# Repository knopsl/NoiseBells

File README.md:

# Noise Bells synthesizer module

This is a percussion and drone synth module based on ideas presented in the 2015 Hackaday article "[Logic noise: More CMOS cowbell!](https://hackaday.com/2015/04/10/logic-noise-more-cmos-cowbell/)" by Elliot Williams. The PCB and front panel are Kosmo format but the same circuit could be implemented in Eurorack format, or other ±12V formats, with no changes other than PCB, panel, and jack dimensions.

The module consists of two separate sections. One is a 2-oscillator circuit based on the "cowbell" section of the Hackaday article. The other is a 4-oscillator circuit, lying sort of halfway between the "cowbell" and "hi hat" designs and designed to use most of the IC functionality left over from the "cowbell" side. Whether it leans more toward bell or cymbal sounds I leave for you to decide. The two sections differ only in the number of oscillators and XORs used.

Aside from a few component value changes, notably a larger capacitor allowing longer decay times, there are a couple of significant modifications to Williams's design:

* The 2-diode "VCA" has been replaced by a 4066 analog switch "VCA" as discussed in the article's comments and at [http://files.electro-music.com/forum/viewtopic.php?highlight=diode+vca&t=23960](http://files.electro-music.com/forum/viewtopic.php?highlight=diode+vca&t=23960). 
* A switch has been added to bypass the EG/VCA section, sending the output of the final XOR straight to the output buffer. This allows using the module for noisy drones.

Pots are used for variable oscillator frequencies and amplitude envelope decay rates. Trigger B input is normalled to Trigger A.

For BOM, schematics, and PCB layout see the [Docs](Docs) folder. The build should be entirely straightforward except, on the first run boards, for the issues mentioned below. Presumably any small signal NPN transistor can be substituted for the 2N3904, though I have not tested any others. 

**Note:** On the first run PCBs the delay pots are connected incorrectly. To fix this, bend the middle leg up and solder it to the leg on its right (pin 2 to pin 3):

This is only for the two delay pots. The six oscillator frequency pots are okay.

Also two capacitors are marked '10uF (47uF?)'. These are 10µF. Unless you like 47µF better of course.

These problems are corrected in the current version.

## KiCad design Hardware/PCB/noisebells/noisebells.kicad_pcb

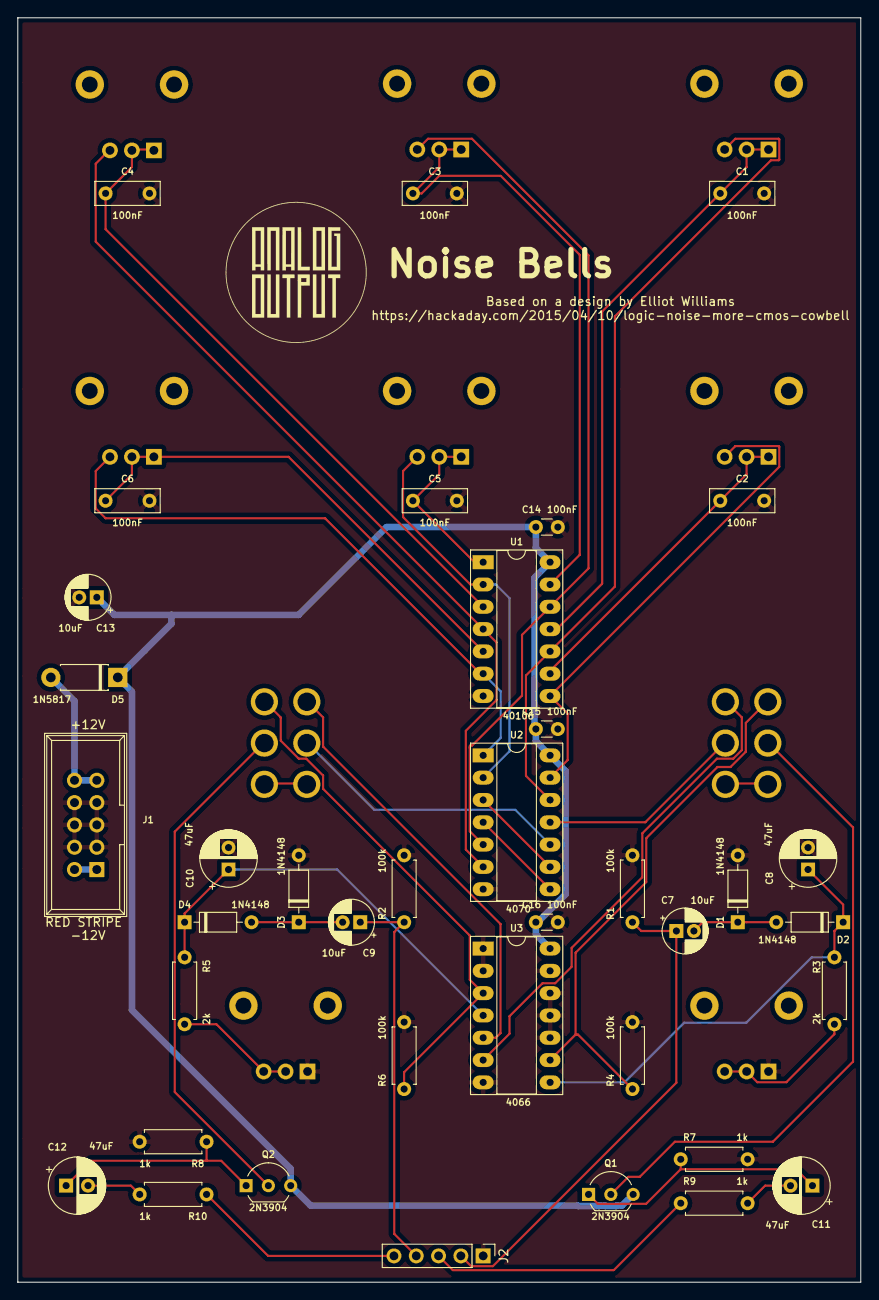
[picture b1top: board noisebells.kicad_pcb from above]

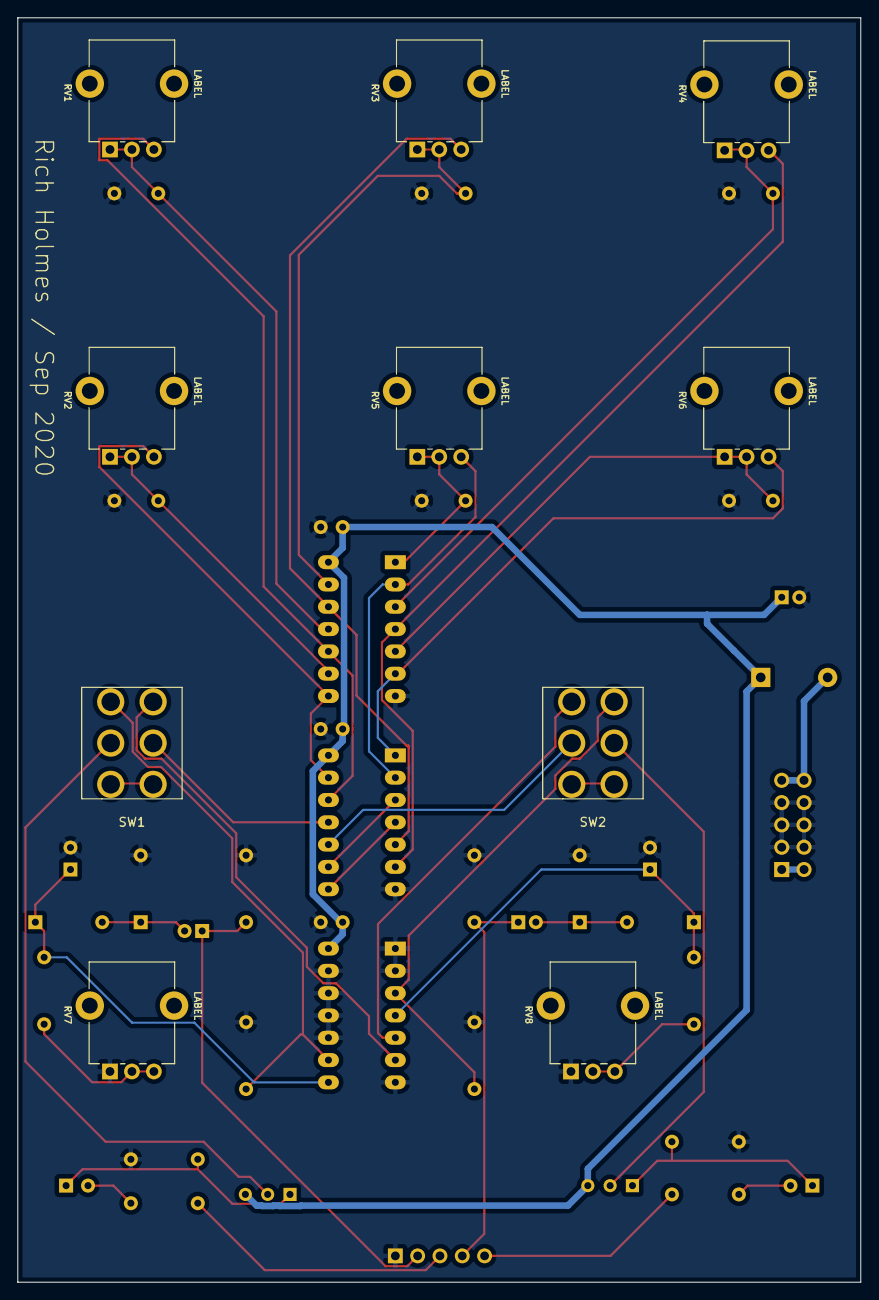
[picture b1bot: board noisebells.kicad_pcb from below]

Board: 2 copper layers, 96.0 x 144.0 mm, 48 parts (10 on the bottom side), 42 nets.

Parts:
C1, C2, C3, C4, C5, C6: 100nF; C_Rect_L7.2mm_W2.5mm_P5.00mm_FKS2_FKP2_MKS2_MKP2
C7, C9, C13: 10uF; CP_Radial_D5.0mm_P2.00mm
C8, C10, C11, C12: 47uF; CP_Radial_D6.3mm_P2.50mm
C14, C15, C16: 100nF; C_Disc_D3.0mm_W1.6mm_P2.50mm
D1, D2, D3, D4: 1N4148; D_DO-35_SOD27_P7.62mm_Horizontal
D5: 1N5817; D_DO-41_SOD81_P7.62mm_Horizontal
J1: Synth_power_2x5; Power_Header
J2: Conn_01x05; PinHeader_1x05_P2.54mm_Vertical
Q1, Q2: 2N3904; TO-92_Inline_Wide
R1, R2, R4, R6: 100k; R_Axial_DIN0207_L6.3mm_D2.5mm_P7.62mm_Horizontal
R3, R5: 2k; R_Axial_DIN0207_L6.3mm_D2.5mm_P7.62mm_Horizontal
R7, R8, R9, R10: 1k; R_Axial_DIN0207_L6.3mm_D2.5mm_P7.62mm_Horizontal
RV1, RV2, RV3, RV4, RV5, RV6, RV7, RV8: 100k; Potentiometer_Alpha_RD901F-40-00D_Single_Vertical_CircularH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
SW1, SW2: SW_DPDT_x2; DPDT-toggle-switch-1M-seriesx
U1: 40106; DIP-14_W7.62mm_Socket_LongPads
U2: 4070; DIP-14_W7.62mm_Socket_LongPads
U3: 4066; DIP-14_W7.62mm_Socket_LongPads

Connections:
+12V: C13.1, C14.1, C15.1, C16.1, D5.1, Q1.3, Q2.3, U1.14, U2.14, U3.14
GND: C1.2, C2.2, C3.2, C4.2, C5.2, C6.2, C8.2, C10.2, C13.2, C14.2, C15.2, C16.2, D1.2, D3.2, J1.3, J1.4, J1.5, J1.6, J1.7, J1.8, J2.1, R1.2, R2.2, R4.2, R6.2, R7.2, R8.2, RV7.1, RV8.1, U1.7, U2.7, U3.1, U3.2, U3.7, U3.10, U3.11, U3.12, U3.13
unnamed: C1.1, RV1.1, RV1.2, U1.11
unnamed: C2.1, RV2.1, RV2.2, U1.9
unnamed: C3.1, RV3.1, RV3.2, U1.13
unnamed: C4.1, RV4.1, RV4.2, U1.3
unnamed: C5.1, RV5.1, RV5.2, U1.1
unnamed: C6.1, RV6.1, RV6.2, U1.5
unnamed: C7.2, D1.1, D2.2
unnamed: C8.1, D2.1, R3.1, U3.8
unnamed: C9.2, D3.1, D4.2
unnamed: C10.1, D4.1, R5.1, U3.4
unnamed: C11.1, Q1.1, R7.1
unnamed: C11.2, R9.2
unnamed: C12.1, Q2.1, R8.1
unnamed: C12.2, R10.2
unnamed: D5.2, J1.9, J1.10
unnamed: J1.1, J1.2
unnamed: Q1.2, SW1.2
unnamed: Q2.2, SW2.5
unnamed: R3.2, RV7.2, RV7.3
unnamed: R4.1, SW1.1, U3.9
unnamed: R5.2, RV8.2, RV8.3
unnamed: R6.1, SW2.4, U3.3
unnamed: RV1.3, U1.10, U2.12
unnamed: RV2.3, U1.8, U2.13
unnamed: RV3.3, U1.12, U2.5
unnamed: RV4.3, U1.4, U2.6
unnamed: RV5.3, U1.2, U2.2
unnamed: RV6.3, U1.6, U2.1
unnamed: SW1.3, SW1.6
unnamed: SW1.4, U3.6
unnamed: SW1.5, U2.11
unnamed: SW2.1, U3.5
unnamed: SW2.2, U2.10
unnamed: SW2.3, SW2.6
unnamed: U2.3, U2.9
unnamed: U2.4, U2.8
OUT_A: J2.3, R9.1
OUT_B: J2.5, R10.1
TRIGGER_A: C7.1, J2.2, R1.1
TRIGGER_B: C9.1, J2.4, R2.1

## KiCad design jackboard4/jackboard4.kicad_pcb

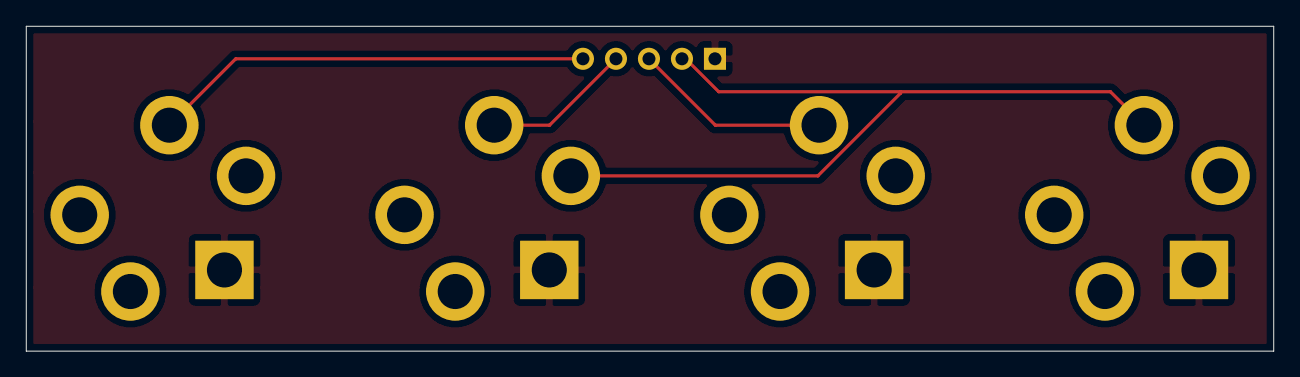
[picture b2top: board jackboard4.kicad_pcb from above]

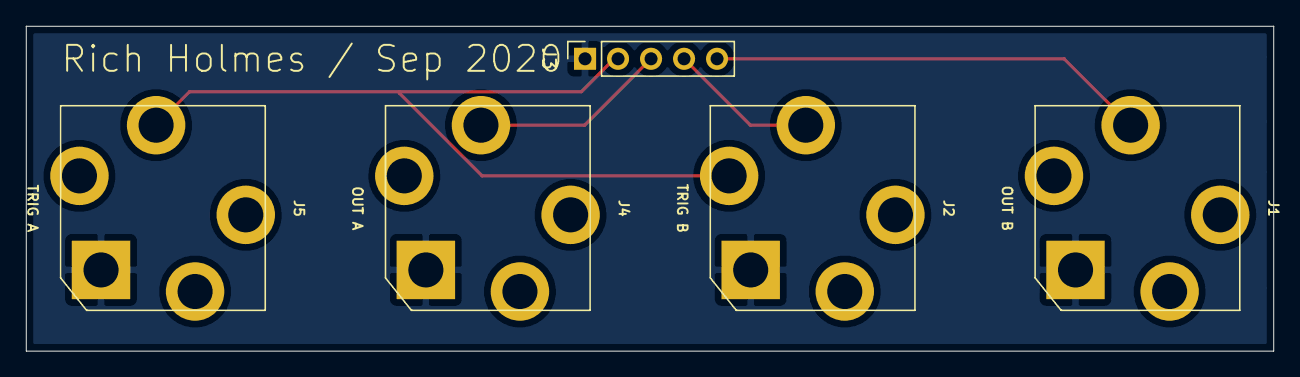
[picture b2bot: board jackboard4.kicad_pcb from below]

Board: 2 copper layers, 96.0 x 25.0 mm, 5 parts (5 on the bottom side), 5 nets.

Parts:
J1, J2, J4, J5: AudioJack2_SwitchT; Jack_6.35mm_PJ_629HAN
J3: Conn_01x05; PinSocket_1x05_P2.54mm_Vertical

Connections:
GND: J1.S, J2.S, J3.1, J4.S, J5.S
unnamed: J1.T, J3.5
unnamed: J2.T, J3.4
unnamed: J2.TN, J3.2, J5.T
unnamed: J3.3, J4.T

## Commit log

2020-10-25 Final design for first run
2020-11-03 Reorg
2020-11-03 BOM, schematics, and layout
2020-11-04 BOM updates, README
2020-11-04 Correct caps value; fix wrong pot direction; move resistor label
2020-11-04 Document preceding issues
2020-11-04 Add credit to Williams
2020-11-05 14 pins, not 16
2020-11-14 README update
2020-11-14 Add photo
2020-11-15 Vendor/cat number info
2020-11-15 Correction on BOM
2020-11-15 Small README updates
2021-01-02 Footprints updated
2021-01-17 Include lib table files
2021-02-19 Footprint update
2021-02-28 Update .gitignore, DIN5
2021-08-07 Kosmo_panel lib update
